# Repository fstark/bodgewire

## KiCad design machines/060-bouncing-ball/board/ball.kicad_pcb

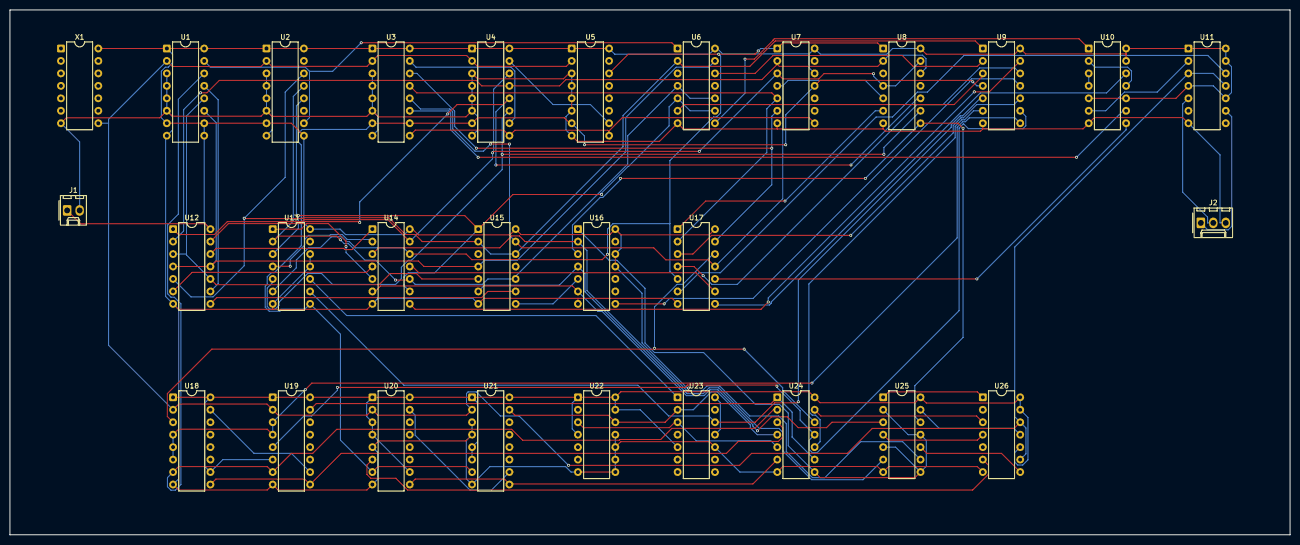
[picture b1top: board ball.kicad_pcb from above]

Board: 2 copper layers, 261.0 x 107.0 mm, 29 parts (0 on the bottom side), 72 nets.

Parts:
J1: POWER; Molex_KK-254_AE-6410-02A_1x02_P2.54mm_Vertical
J2: VIDEO; Molex_KK-254_AE-6410-03A_1x03_P2.54mm_Vertical
U1, U2, U3, U4, U5, U18, U19, U20, U21: 74LS161; DIP-16_W7.62mm
U6, U8, U15: 74LS20; DIP-14_W7.62mm
U7, U16: 74LS30; DIP-14_W7.62mm
U9: 74LS04; DIP-14_W7.62mm
U10: 74LS86; DIP-14_W7.62mm
U11: 74LS74; DIP-14_W7.62mm
U12, U17: 74LS27; DIP-14_W7.62mm
U13, U25: 74LS02; DIP-14_W7.62mm
U14, U24: 74LS00; DIP-14_W7.62mm
U22, U26: 74LS107; DIP-14_W7.62mm
U23: 74LS93; DIP-14_W7.62mm
X1: OSC; DIP-14_W7.62mm

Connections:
BALL_CK: U13.10 (3Y), U23.1 (CKB)
BALL_N: U16.1 (A), U24.8 (3Y), U25.2 (1A), U25.5 (2A), U25.8 (3A), U25.11 (4A)
BALL_OFF: U9.5 (3A), U13.9 (3B), U23.12 (QA)
BALL_QD: U23.11 (QD), U23.14 (CKA)
BHC: U18.15 (RCO), U19.10 (ENT)
BOTTOM_N: U8.8 (2Y), U16.3 (C), U25.12 (4B)
BV8: U22.3 (1Q), U23.3 (R02), U24.5 (2B)
BVC: U20.15 (RCO), U21.10 (ENT)
CLK: U1.2 (CLK), U2.2 (CLK), U3.2 (CLK), U4.2 (CLK), U5.2 (CLK), U11.3 (1CLK), U11.11 (2CLK), U18.2 (CLK), U19.2 (CLK), U20.2 (CLK), U21.2 (CLK), U26.9 (2CLK), U26.12 (1CLK), X1.8 (OUT)
FRAME_END_N: U3.9 (LOAD_N), U4.9 (LOAD_N), U5.9 (LOAD_N), U7.8 (Y)
GND: J1.2 (GND), J2.3 (GND), U1.3 (A), U1.4 (B), U1.5 (C), U1.6 (D), U1.8 (GND), U2.3 (A), U2.4 (B), U2.5 (C), U2.6 (D), U2.8 (GND), U3.3 (A), U3.4 (B), U3.5 (C), U3.6 (D), U3.8 (GND), U4.3 (A), U4.4 (B), U4.5 (C), U4.6 (D), U4.8 (GND), U5.3 (A), U5.4 (B), U5.5 (C), U5.6 (D), U5.8 (GND), U6.7 (GND), U7.7 (GND), U8.7 (GND), U9.7 (GND), U10.7 (GND), U11.7 (GND), U12.7 (GND), U13.7 (GND), U13.11 (4A), U13.12 (4B), U14.7 (GND), U15.7 (GND), U16.7 (GND), U17.7 (GND), U18.8 (GND), U19.8 (GND), U20.5 (C), U20.8 (GND), U21.3 (A), U21.4 (B), U21.8 (GND), U22.7 (GND), U22.8 (2J), U22.9 (2CLK), U22.10 (2CLR_N), U22.11 (2K), U23.10 (GND), U24.7 (GND), U25.7 (GND), U26.7 (GND), X1.7 (GND)
H0: U1.14 (QA), U18.7 (ENP), U19.7 (ENP), U24.2 (1B)
H1: U1.13 (QB), U12.9 (3A)
H2: U1.12 (QC), U12.3 (2A), U12.10 (3B), U15.5 (1D)
H3: U1.11 (QD), U6.13 (2D), U12.4 (2B), U12.11 (3C), U15.4 (1C)
H4: U2.14 (QA), U6.2 (1B), U9.1 (1A), U12.5 (2C), U15.2 (1B), U15.12 (2C)
H4_N: U6.12 (2C), U9.2 (1Y)
H5: U2.13 (QB), U6.4 (1C), U6.10 (2B), U13.2 (1A), U14.10 (3B), U15.10 (2B)
H6: U2.12 (QC), U6.5 (1D), U6.9 (2A), U13.3 (1B), U14.9 (3A), U15.1 (1A)
H56_LOW: U13.1 (1Y), U14.5 (2B)
HBALL: U19.15 (RCO), U24.1 (1A), U24.9 (3A)
HBLANK: U9.12 (6Y), U17.4 (2B)
HBLANK_N: U9.13 (6A), U14.8 (3Y)
HC: U1.15 (RCO), U2.10 (ENT), U6.1 (1A)
HDIR: U24.13 (4B), U26.3 (1Q)
HIT_BOTTOM: U25.13 (4Y), U26.11 (2K)
HIT_LEFT: U25.1 (1Y), U26.1 (1J)
HIT_RIGHT: U25.4 (2Y), U26.4 (1K)
HIT_TOP: U25.10 (3Y), U26.8 (2J)
HLOAD_N: U18.9 (LOAD_N), U19.9 (LOAD_N), U24.3 (1Y)
HSYNC_N: U6.8 (2Y), U10.1 (1A)
LEFT_A: U12.6 (2Y), U14.4 (2A)
LEFT_N: U14.6 (2Y), U16.6 (F), U25.3 (1B)
LINE_END: U3.7 (ENP), U3.10 (ENT), U4.7 (ENP), U5.7 (ENP), U7.11 (G), U9.4 (2Y), U13.8 (3A), U20.7 (ENP), U21.7 (ENP)
LINE_END_N: U6.6 (1Y), U9.3 (2A)
MIX: U9.11 (5A), U16.8 (Y)
MIX_N: U9.10 (5Y), U17.3 (2A)
MOVE: U17.12 (1Y), U18.3 (A), U24.12 (4A)
MR: U9.8 (4Y), U18.4 (B), U18.5 (C), U18.6 (D), U19.3 (A), U19.4 (B)
MR_N: U9.9 (4A), U19.5 (C), U24.11 (4Y)
NET_A: U12.8 (3Y), U15.9 (2A)
NET_N: U15.8 (2Y), U16.5 (E)
RIGHT_N: U15.6 (1Y), U16.4 (D), U25.6 (2B)
SYNC: U10.3 (1Y), U10.4 (2A)
SYNC_N: J2.2 (SYNC_N), U11.5 (1Q)
SYNC_N_D: U10.6 (2Y), U11.2 (1D)
TICK_N: U8.6 (1Y), U17.1 (1A)
TOP_A: U12.12 (1Y), U14.1 (1A)
TOP_B: U13.4 (2Y), U14.2 (1B)
TOP_N: U14.3 (1Y), U16.2 (B), U25.9 (3B)
V0: U3.14 (QA), U7.6 (F), U17.13 (1C)
V1: U3.13 (QB), U7.5 (E), U17.2 (1B)
V2: U3.12 (QC), U7.4 (D), U8.5 (1D), U15.13 (2D), U17.11 (3C)
V3: U3.11 (QD), U10.9 (3A)
V3_N: U10.8 (3Y), U17.10 (3B)
V4: U4.14 (QA), U7.3 (C), U8.4 (1C), U8.13 (2D), U12.1 (1A), U14.13 (4B)
V5: U4.13 (QB), U7.2 (B), U8.2 (1B), U8.12 (2C), U12.2 (1B)
V6: U4.12 (QC), U8.10 (2B), U12.13 (1C)
V7: U4.11 (QD), U8.9 (2A), U13.5 (2A)
V8: U5.14 (QA), U7.1 (A), U8.1 (1A), U13.6 (2B), U14.12 (4A), U17.5 (2C)
VBALL: U9.6 (3Y), U24.10 (3B)
VC1: U3.15 (RCO), U4.10 (ENT)
VC2: U4.15 (RCO), U5.10 (ENT)
VCC: J1.1 (VCC), U1.1 (CLR_N), U1.7 (ENP), U1.9 (LOAD_N), U1.10 (ENT), U1.16 (VCC), U2.1 (CLR_N), U2.7 (ENP), U2.9 (LOAD_N), U2.16 (VCC), U3.1 (CLR_N), U3.16 (VCC), U4.1 (CLR_N), U4.16 (VCC), U5.1 (CLR_N), U5.16 (VCC), U6.14 (VCC), U7.12 (H), U7.14 (VCC), U8.14 (VCC), U9.14 (VCC), U10.5 (2B), U10.10 (3B), U10.13 (4B), U10.14 (VCC), U11.1 (1CLR_N), U11.4 (1PRE_N), U11.10 (2PRE_N), U11.13 (2CLR_N), U11.14 (VCC), U12.14 (VCC), U13.14 (VCC), U14.14 (VCC), U15.14 (VCC), U16.11 (G), U16.12 (H), U16.14 (VCC), U17.14 (VCC), U18.1 (CLR_N), U18.10 (ENT), U18.16 (VCC), U19.1 (CLR_N), U19.6 (D), U19.16 (VCC), U20.1 (CLR_N), U20.3 (A), U20.4 (B), U20.10 (ENT), U20.16 (VCC), U21.1 (CLR_N), U21.5 (C), U21.6 (D), U21.16 (VCC), U22.1 (1J), U22.4 (1K), U22.13 (1CLR_N), U22.14 (VCC), U23.5 (VCC), U24.14 (VCC), U25.14 (VCC), U26.10 (2CLR_N), U26.13 (1CLR_N), U26.14 (VCC), X1.14 (VCC)
VDIR_N: U20.6 (D), U26.6 (2Q_N)
VIDEO: J2.1 (VIDEO), U11.9 (2Q)
VIDEO_D: U11.12 (2D), U17.6 (2Y)
VLOAD_N: U20.9 (LOAD_N), U21.9 (LOAD_N), U24.6 (2Y)
VRCO: U21.15 (RCO), U22.12 (1CLK), U23.2 (R01), U24.4 (2A)
VSYNC: U10.12 (4A), U17.8 (3Y)
VSYNC_A: U14.11 (4Y), U17.9 (3A)
VSYNC_N: U10.2 (1B), U10.11 (4Y)
